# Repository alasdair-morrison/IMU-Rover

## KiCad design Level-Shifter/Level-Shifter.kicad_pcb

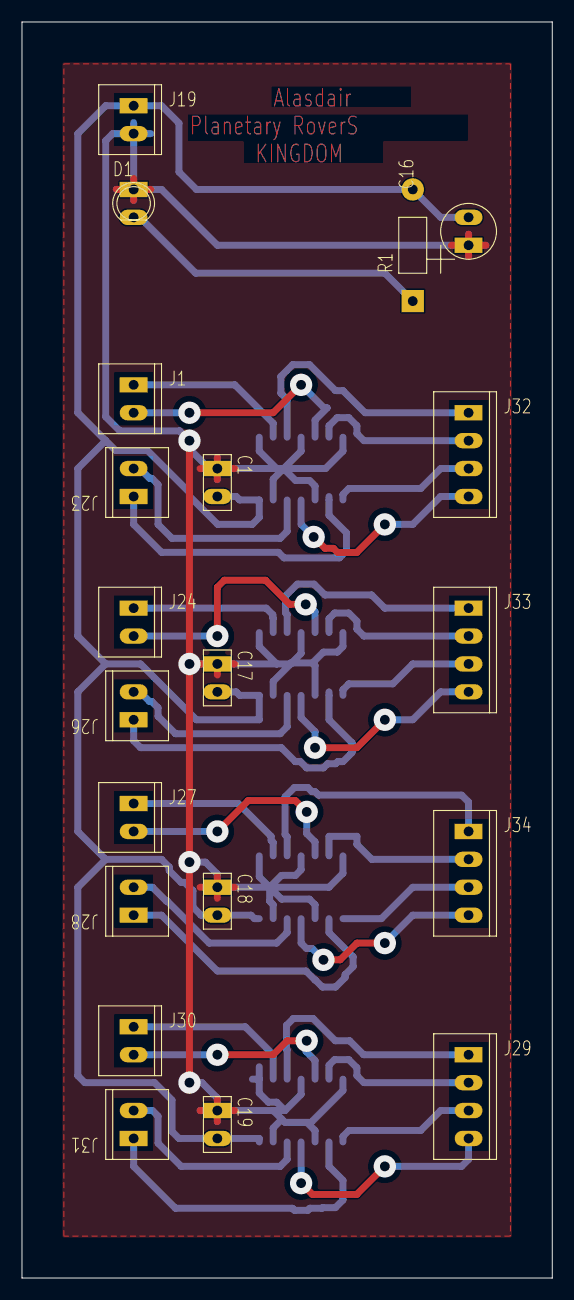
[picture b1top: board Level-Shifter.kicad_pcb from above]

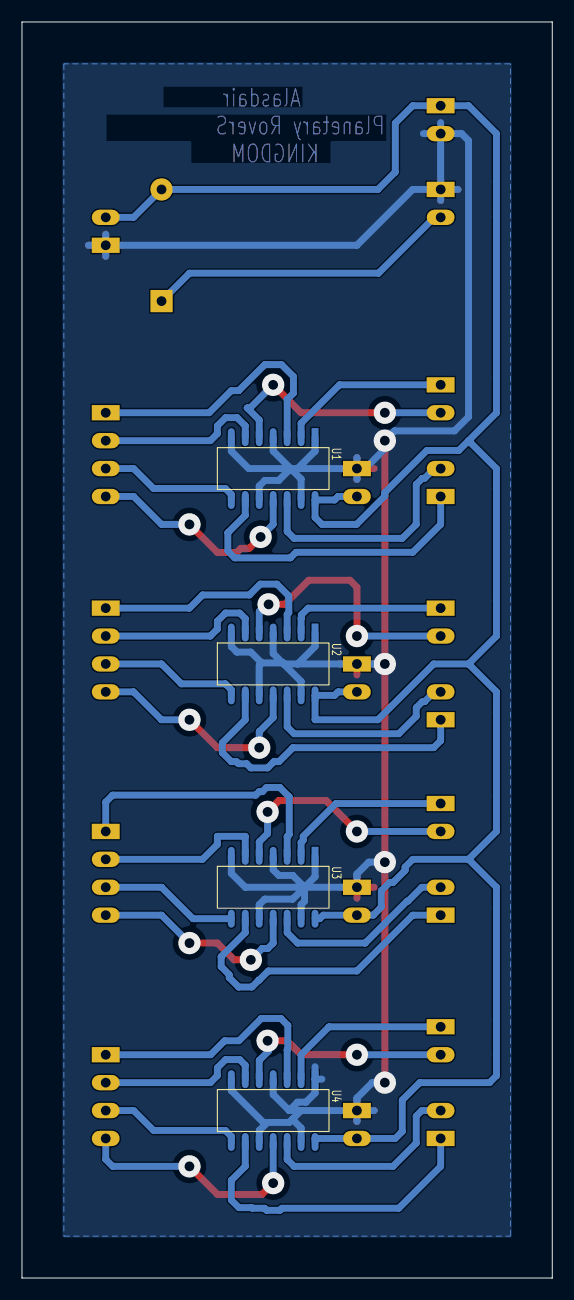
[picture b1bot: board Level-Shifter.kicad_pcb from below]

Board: 2 copper layers, 48.3 x 114.3 mm, 24 parts (4 on the bottom side), 35 nets.

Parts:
C1, C16, C17, C18, C19: (no value)
D1: (no value)
J1, J19, J23, J24, J26, J27, J28, J29, J30, J31, J32, J33, J34: (no value)
R1: (no value)
U1, U2, U3, U4: (no value)

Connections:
3V3: C1.2, C16.2, C17.2, C18.2, C19.2, J19.1, R1.2, U1.14, U2.14, U3.14, U4.14
GND: C1.1, C16.1, C17.1, C18.1, C19.1, D1.1, J19.2, U1.1, U1.4, U1.7, U1.10, U1.13, U2.1, U2.4, U2.7, U2.10, U2.13, U3.1, U3.4, U3.7, U3.10, U3.13, U4.1, U4.4, U4.7, U4.10, U4.13
N18974: J32.1, U1.3
N24239: J1.1, U1.2
N24252: J1.2, U1.5
N123386: J32.2, U1.6
N123809: J23.1, U1.9
N123817: J32.3, U1.8
N123893: J23.2, U1.12
N123943: J32.4, U1.11
N125496: J24.1, U2.2
N125504: J33.1, U2.3
N125580: J24.2, U2.5
N125630: J33.2, U2.6
N127030: J26.1, U2.9
N127038: J33.3, U2.8
N127114: J26.2, U2.12
N127168: J33.4, U2.11
N127262: J27.1, U3.2
N127270: J34.1, U3.3
N127346: J27.2, U3.5
N127400: J34.2, U3.6
N127494: J28.1, U3.9
N127502: J34.3, U3.8
N127602: J28.2, U3.12
N127684: J34.4, U3.11
N133045: J30.1, U4.2
N133053: J29.1, U4.3
N133129: J30.2, U4.5
N133179: J29.2, U4.6
N133269: J31.1, U4.9
N133277: J29.3, U4.8
N133353: J31.2, U4.12
N133403: J29.4, U4.11
N144791: D1.2, R1.1

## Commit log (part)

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2026-02-02 basic PWM code for one motor
2026-02-02 changed pwm pin out
2026-02-02 added second motor control for testing
2026-02-23 fully working code to run all motors at full speed
2026-03-16 seperated forward drive file from test file
2026-03-16 functional pwm through register control for all dedicated pins
2026-03-16 transfered PWM functionality into forward driving code. Functional
2026-03-16 Rover running under full PWM Control
2026-03-16 moved enable pins away from datalogger to test. Not tested
2026-03-17 Moved all motor control off of encoder shield. Functional
2026-03-19 added pins for encoders and IMU
2026-03-19 fixed port allocations and begun testing datalogger
2026-03-19 fully functional datalogger recording in test
2026-04-20 added file implementing Ammar's encoder & IMU sensing
2026-04-20 fixed comments in some files
2026-06-19 Add initial implementation for motor control and logging
